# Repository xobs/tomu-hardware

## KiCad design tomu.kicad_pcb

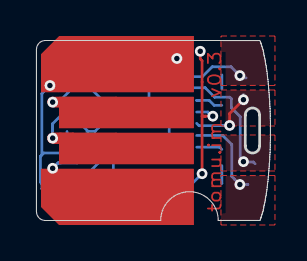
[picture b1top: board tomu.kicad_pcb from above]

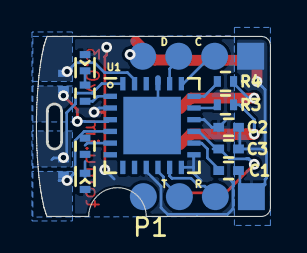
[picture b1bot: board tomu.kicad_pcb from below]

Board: 2 copper layers, 13.0 x 10.0 mm, 15 parts (14 on the bottom side), 21 nets.

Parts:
C1, C2: 1uF; C_0402
C3: 4.7uF; C_0402
D1, D2: LED; LED_0402
P1: USART0; SMT-4pin
P2: DEBUG; debug-points
P3: USB-PCB
R1, R2: 75; R_0402
R3, R4: 15; R_0402
U1: EFM32HG309; QFN-24-1EP_5x5mm_Pitch0.65mm
W1: CAP0; minimal-points
W2: CAP1; minimal-points

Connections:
+3V3: C2.1, D1.2, D2.2, U1.2, U1.9, U1.12, U1.13, U1.16, U1.22
/CAP0A: U1.3, W1.2
/CAP0B: U1.23, W1.1
/CAP1A: U1.4, W2.2
/CAP1B: U1.24, W2.1
/DBG_SWCLK: P2.2, U1.19
/DBG_SWDIO: P2.3, U1.20
/DEC: C1.2, U1.14
/LED0: R2.2, U1.5
/LED1: R1.1, U1.1
/LEU0_RX: P1.2, U1.11
/LEU0_TX: P1.3, U1.10
/RUSB_D+: R4.2, U1.18
/RUSB_D-: R3.2, U1.17
/USB_5V: C3.1, P3.1, U1.15
/USB_D+: P3.3, R4.1
/USB_D-: P3.2, R3.1
GND: C1.1, C2.2, C3.2, P1.1, P2.1, P3.4, U1.21, U1.25
unnamed: D1.1, R1.2
unnamed: D2.1, R2.1
unnamed: P2.4, U1.7

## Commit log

2018-01-09 wip commit: half-done rework
    The big difference with v0.4 is a large cutout on the side to facilitate
    mating with an enclosure. This necessitates many changes to the board
    layout.

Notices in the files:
tomu.kicad_pcb:
License: CC-BY-SA 4.0 or TAPR
